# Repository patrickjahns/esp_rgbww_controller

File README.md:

# ESP8266 WiFi RGBWW LED Dimmer v1.5
Custom Hardware board for controlling 5 Led Channels via PWM (RGB + Warm/Cold White). It is designed for max current ~4.5A per Channel.

# Changelog

* 1.5 (31.01.2017)
  * DCDC wandler has been remeasured and provided for through hole mounting on pin headers
  * Jumper introduced for allowing for external 3,3V connections
  * measurements have been changed to 53mm*47mm with mounting holes tailored towards "Strapubox CO 4" casing
  * C1 has been replaced with a smaller form factor

* 1.3 (20.02.2016)
  * added another tact switch which can be used during boot to reset settings
  * silksceen naming updated 

* 1.2 (16.02.2016)
  * improved the layout for better EMV
  * added buffer capacitor for dc converter
  * added filter capacitor close to ESP8266
  
* 1.1 (01.02.2016)
  * connected ADC 
  * some layout improvements

# Parts
- 1x ESP8266, ESP-12 format
- 1x XM1584 Power converter (set to 3.3v!)
- 5x IRLZ44N Mosfet (logic level gate threshold)
- 11x 10k resistors, 0805 (R1 - R11)
- 1x 1k resistors, 0805 (R12)
- 1x 330 µF Elko RM 2.5 mm (C1) 
- 1x 100 µF Elko RM 2.5 mm (C3)
- 1x 100 nF capacitor 0805(C2)
- 3x 5,08mm 2pin terminal block
- 1x 5,08mm 3pin terminal block
- 1x 2,54mm 4pin header
- 2x Micro SMD Tact Switch 2 pin 3*6*2.5 mm (optional)

# Assembly
Assembly of the PCB Board is straight forward, solder all parts to the PCB.

__Caution :__ before soldering the esp module to the PCB, set the output voltage of XM1584 converter  to 3.3v

### Recommended steps
- Start with soldering the smd resistors
- __Ensure the output voltage of XM1584 converter is 3.3v before continuing__. 
- Solder the XM1584 Power Board 
- Solder ESP8266 Module 
- Optional: solder SMD Tact Switch
- Solder Elkos
- Solder Terminal Blocks, 4pin header 
- Solder FETs

# Firmware
Firmware is still work in progress.

Latest can be found here:
https://github.com/patrickjahns/esp_rgbww_controller_fw

# Modifying
The schematic and board files are compatible with eagle 7.2+

## Ideas
Here are some ideas for future revisions
- see if we can clear some GPIOs and provide them via PIN Header for other enhancements (i.e. IR / Rotary Controller) 
- change layout for VCC/GND to be on the left side
- ~~connect ADC to detect power failure~~ 

# Resources
* [ESP RGB Project](https://github.com/RiRomain/esp-dimmer-hardware)
* [H801 Wifi Controller Hack](http://chaozlabs.blogspot.de/2015/08/esp8266-in-wild-wifi-led-controller-hack.html)

# Thread in Fhem Forum
* [Entwicklung/Sammelbestellung RGBWW Wifi Led Controller](https://forum.fhem.de/index.php/topic,48918.msg)

# Credits
Thanks to RiRomain for his excellent documentated [ESP RGB Project](https://github.com/RiRomain/esp-dimmer-hardware)

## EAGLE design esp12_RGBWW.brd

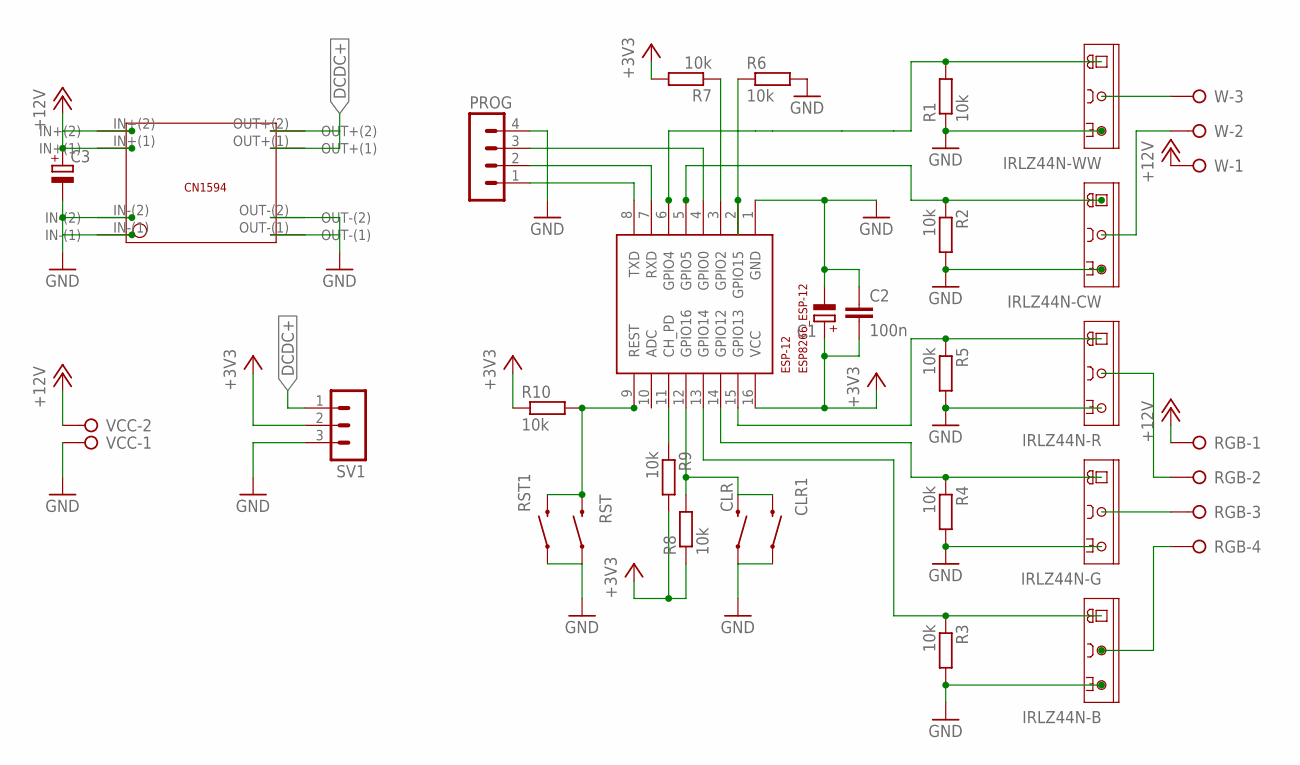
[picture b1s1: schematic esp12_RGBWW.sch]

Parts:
C1, C3: CPOL-EUE2.5-6; E2,5-6
C2: 100n; C0805
CLR, CLR1: SWITCH-MOMENTARY-2SMD-1101NE; TACTILE-SWITCH-1101NE
ESP-12: ESP8266_ESP-12; ESP8266-ESP12
IRLZ44N-B, IRLZ44N-CW, IRLZ44N-G, IRLZ44N-R, IRLZ44N-WW: TIP121; TO220AV
PROG: MA04-1
R1, R2, R3, R4, R5, R6, R7, R8, R9, R10: 10k; R0805
RGB: W237-04P; W237-4P
RST, RST1: SWITCH-MOMENTARY-2SMD-1101NE; TACTILE-SWITCH-1101NE
SV1: MA03-1
U$2: XM1584; XM1584-TH
VCC: W237-02P; W237-132
W: W237-03P; W237-133

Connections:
+3V3: C1.+, C2.2, ESP-12.16 (VCC), R7.2, R8.1, R9.2, R10.1, SV1.2
+12V: C3.+, RGB.1, U$2.IN+(1), U$2.IN+(2), VCC.2, W.1
DCDC+: SV1.1, U$2.OUT+(1), U$2.OUT+(2)
GND: C1.-, C2.1, C3.-, CLR.1, CLR1.1, ESP-12.1 (GND), IRLZ44N-B.E, IRLZ44N-CW.E, IRLZ44N-G.E, IRLZ44N-R.E, IRLZ44N-WW.E, PROG.4, R1.1, R2.2, R3.2, R4.2, R5.2, R6.2, RST.1, RST1.1, SV1.3, U$2.IN-(1), U$2.IN-(2), U$2.OUT-(1), U$2.OUT-(2), VCC.1
unnamed: CLR.2, CLR1.2, ESP-12.12 (GPIO16), R8.2
unnamed: ESP-12.11 (CH_PD), R9.1
unnamed: ESP-12.3 (GPIO2), R7.1
unnamed: ESP-12.7 (RXD), PROG.2
unnamed: ESP-12.2 (GPIO15), R6.1
unnamed: ESP-12.8 (TXD), PROG.1
unnamed: ESP-12.4 (GPIO0), PROG.3
unnamed: ESP-12.9 (REST), R10.2, RST.2, RST1.2
RGB-B: ESP-12.13 (GPIO14), IRLZ44N-B.B, R3.1
RGB-B-OUT: IRLZ44N-B.C, RGB.4
RGB-CW: ESP-12.5 (GPIO5), IRLZ44N-CW.B, R2.1
RGB-CW-OUT: IRLZ44N-CW.C, W.2
RGB-G: ESP-12.14 (GPIO12), IRLZ44N-G.B, R4.1
RGB-G-OUT: IRLZ44N-G.C, RGB.3
RGB-R: ESP-12.15 (GPIO13), IRLZ44N-R.B, R5.1
RGB-R-OUT: IRLZ44N-R.C, RGB.2
RGB-WW: ESP-12.6 (GPIO4), IRLZ44N-WW.B, R1.2
RGB-WW-OUT: IRLZ44N-WW.C, W.3

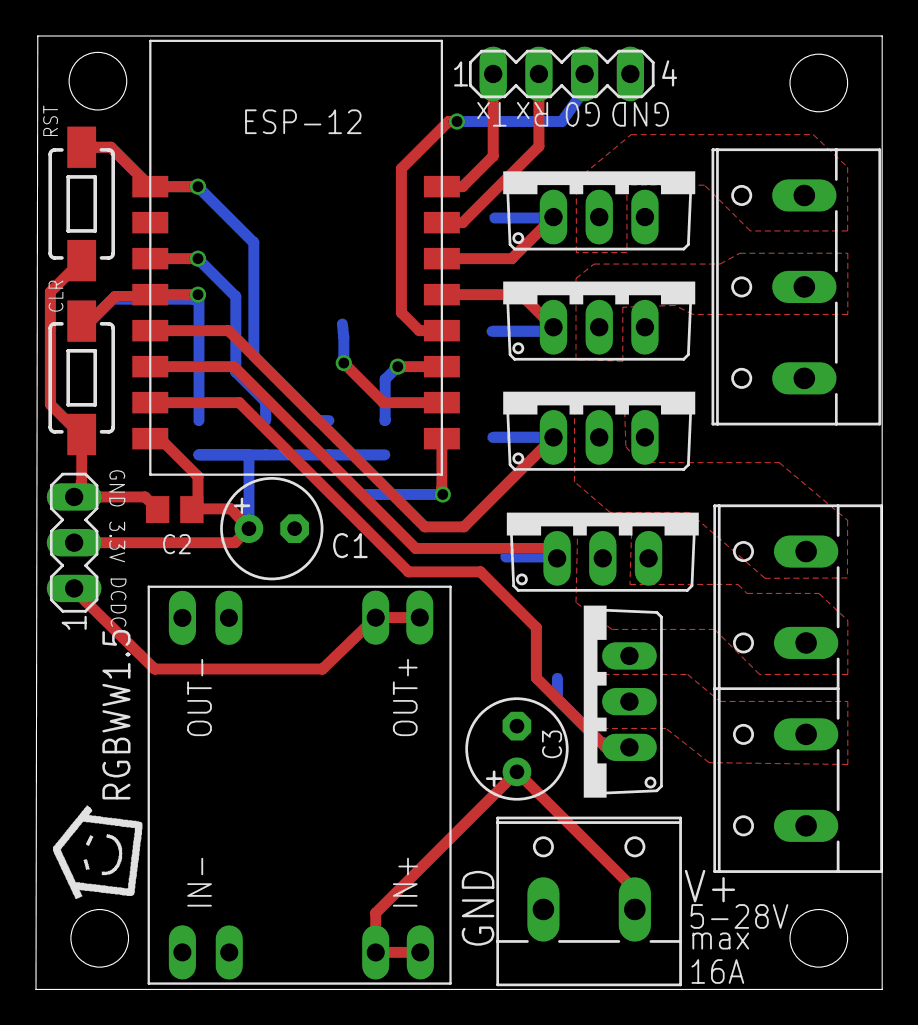
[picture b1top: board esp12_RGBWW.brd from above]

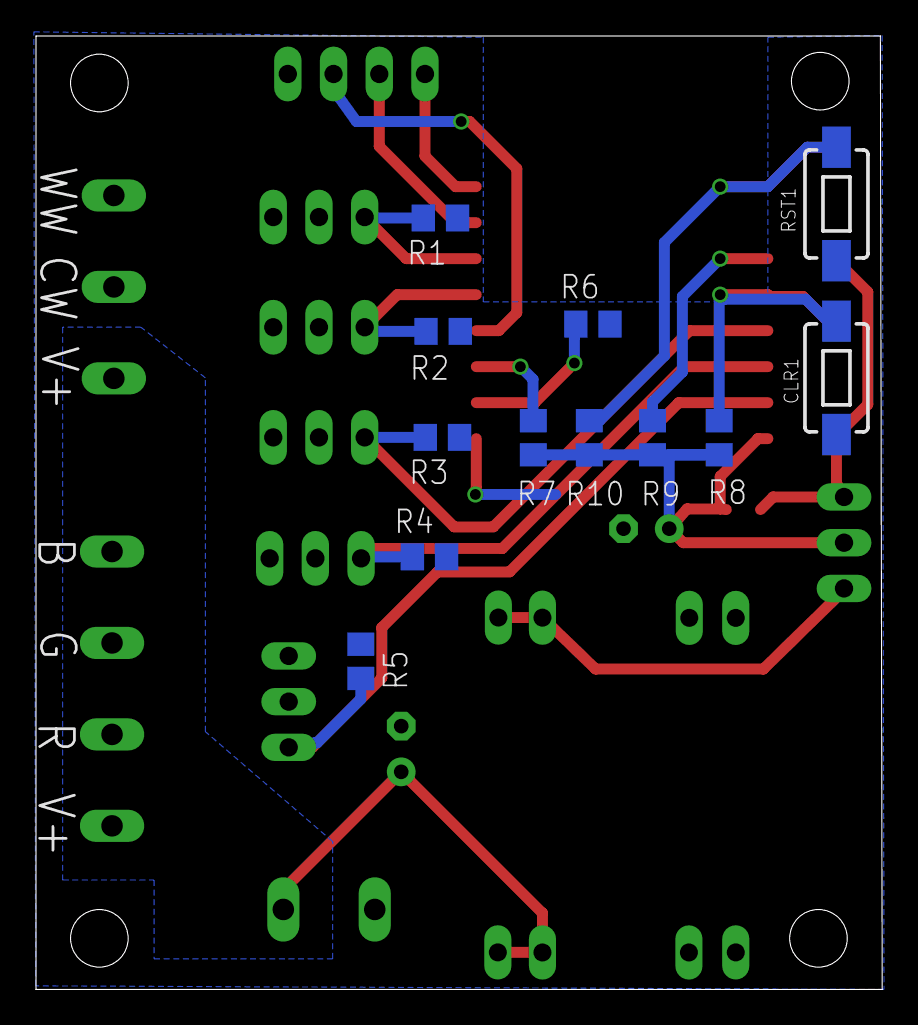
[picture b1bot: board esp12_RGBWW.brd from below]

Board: 2 copper layers, 47.0 x 53.0 mm, 30 parts (12 on the bottom side), 22 nets.

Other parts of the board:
U$1: LOGO

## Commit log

2016-02-02 updated board
2016-02-02 added gerber files
2016-02-05 added ADC and updated board layout
2016-02-05 updated picture
2016-02-05 added eagle .lck files to gitignore
2016-02-16 v1.2
2016-02-16 small cosmetic corrections
2016-02-16 MOSFET netclass renamed
2016-02-16 updated pictures
2016-02-16 cosmetics
2016-02-17 typo
2016-02-20 v1.3
2016-02-20 updated gerber files
2016-02-20 added 3d pcb renderings
2016-03-04 updated silkscreen
2016-03-30 Added some ideas for future revision
2016-04-16 Update README.md
    fix typo
2016-04-16 Added files via upload
    add some pictures
2016-04-16 Update README.md
    fixed C1
2016-04-16 Update README.md
    Add link to fhem forum thread
2017-01-31 CN1594 library exchanged with a more specific xm1584 library which also features through hole mounting
2017-01-31 remove old pictures
2017-01-31 new pictures
2017-01-31 updated schematics and board v1.5
2017-01-31 gerber files for layout 1.5
2017-01-31 updated with changes for v1.5

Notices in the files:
parts and their libraries:
SparkFun-Electromechanical: Licensing: Creative Commons ShareAlike 4.0 International - https://creativecommons.org/licenses/by-sa/4.0
